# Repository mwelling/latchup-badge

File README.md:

# Fossi LATCH-UP Badge (Unofficial)

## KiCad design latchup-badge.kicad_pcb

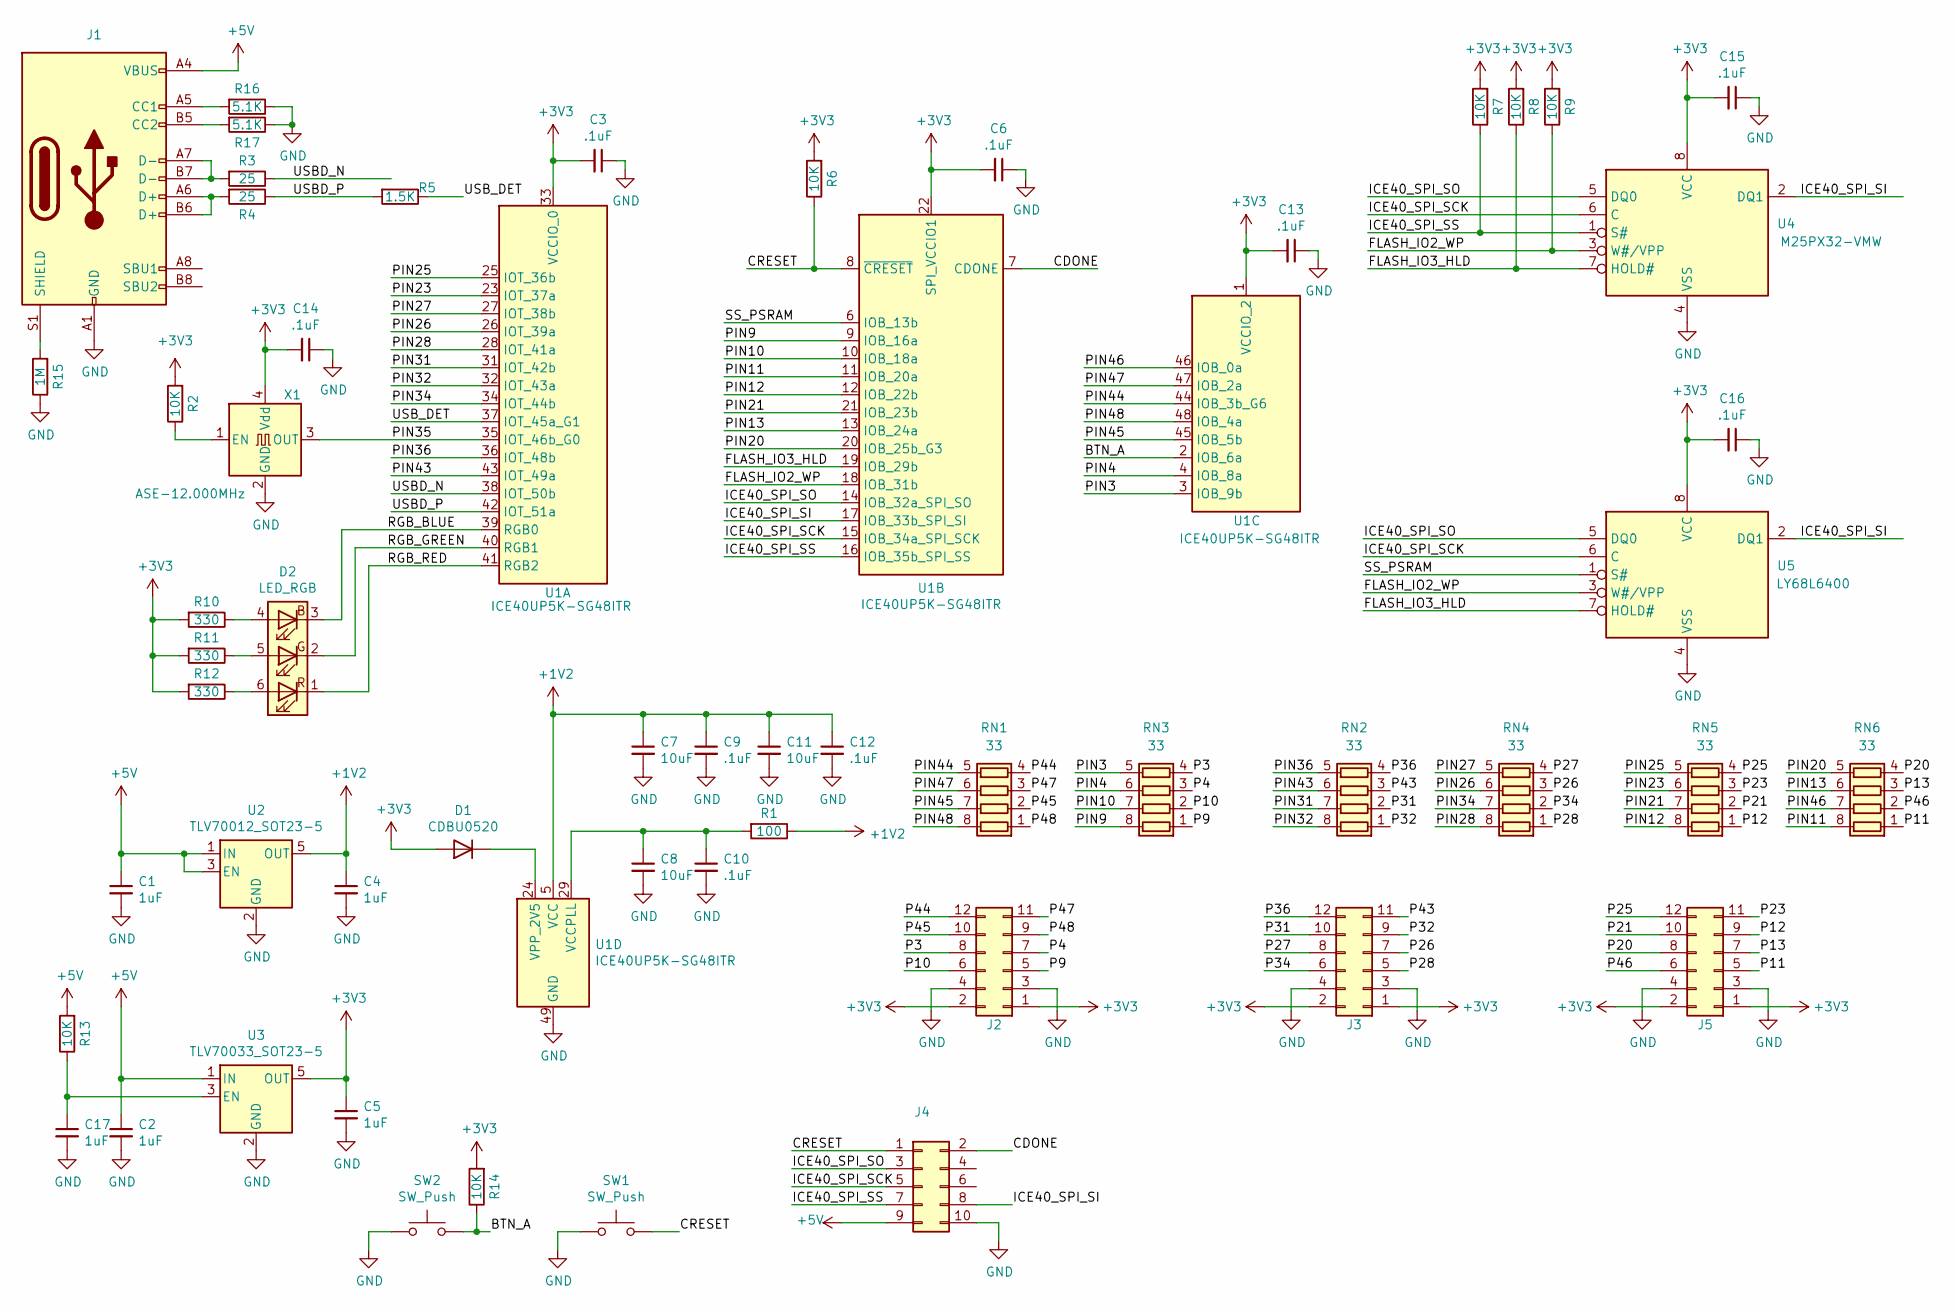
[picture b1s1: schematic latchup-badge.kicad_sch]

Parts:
C1, C2, C4, C5, C17: 1uF; C_0603_1608Metric
C3, C6, C9, C10, C12, C13, C14, C15, C16: .1uF; C_0402_1005Metric
C7, C8, C11: 10uF; C_0603_1608Metric
D1: CDBU0520; D_0603_1608Metric
D2: LED_RGB; LED_RGB_PLLC-6
J1: USB_C_Receptacle_USB2.0; USB_C_Receptacle_HRO_TYPE-C-31-M-12
J2, J3, J5: Connector_Generic:Conn_02x06_Odd_Even; PinSocket_2x06_P2.54mm_Horizontal
J4: Connector_Generic:Conn_02x05_Odd_Even; PinSocket_2x05_P2.54mm_Vertical
R1: 100; R_0402_1005Metric
R2, R6, R7, R8, R9, R13, R14: 10K; R_0402_1005Metric
R3, R4: 25; R_0402_1005Metric
R5: 1.5K; R_0402_1005Metric
R10, R11, R12: 330; R_0402_1005Metric
R15: 1M; R_0402_1005Metric
R16, R17: 5.1K; R_0402_1005Metric
RN1, RN2, RN3, RN4, RN5, RN6: 33; R_Array_Concave_4x0402
SW1, SW2: SW_Push; SW_SPST_EVQQ2
U1: ICE40UP5K-SG48ITR; QFN-48-1EP_7x7mm_P0.5mm_EP5.6x5.6mm
U2: TLV70012_SOT23-5; SOT-23-5
U3: TLV70033_SOT23-5; SOT-23-5
U4: M25PX32-VMW; SOIC-8W_5.3x5.3mm_P1.27mm
U5: LY68L6400; SOIC-8_3.9x4.9mm_P1.27mm
X1: ASE-12.000MHz; Oscillator_SMD_Abracon_ASE-4Pin_3.2x2.5mm

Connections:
+1V2: C4.1, C7.1, C9.1, C11.1, C12.1, R1.1, U1.5 (VCC), U1.30 (VCC), U2.5 (OUT)
+3V3: C3.2, C5.1, C6.2, C13.2, C14.2, C15.2, C16.2, D1.2 (A), J2.1, J2.2, J3.1, J3.2, J5.1, J5.2, R2.2, R6.2, R7.2, R8.2, R9.2, R10.2, R11.2, R12.2, R14.2, U1.1 (VCCIO_2), U1.22 (SPI_VCCIO1), U1.33 (VCCIO_0), U3.5 (OUT), U4.8 (VCC), U5.8 (VCC), X1.4 (Vdd)
+5V: C1.1, C2.1, J1.A4 (VBUS), J1.A9 (VBUS), J1.B4 (VBUS), J1.B9 (VBUS), J4.9, R13.2, U2.1 (IN), U2.3 (EN), U3.1 (IN)
/BTN_A: R14.1, SW2.2, U1.2 (IOB_6a)
/CDONE: J4.2, U1.7 (CDONE)
/CRESET: J4.1, R6.1, SW1.2, U1.8 (~CRESET)
/FLASH_IO2_WP: R9.1, U1.18 (IOB_31b), U4.3 (W#/VPP), U5.3 (W#/VPP)
/FLASH_IO3_HLD: R8.1, U1.19 (IOB_29b), U4.7 (HOLD#), U5.7 (HOLD#)
/ICE40_SPI_SCK: J4.5, U1.15 (IOB_34a_SPI_SCK), U4.6 (C), U5.6 (C)
/ICE40_SPI_SI: J4.8, U1.17 (IOB_33b_SPI_SI), U4.2 (DQ1), U5.2 (DQ1)
/ICE40_SPI_SO: J4.3, U1.14 (IOB_32a_SPI_SO), U4.5 (DQ0), U5.5 (DQ0)
/ICE40_SPI_SS: J4.7, R7.1, U1.16 (IOB_35b_SPI_SS), U4.1 (S#)
/P3: J2.8, RN3.4 (R4.1)
/P4: J2.7, RN3.3 (R3.1)
/P9: J2.5, RN3.1 (R1.1)
/P10: J2.6, RN3.2 (R2.1)
/P11: J5.5, RN6.1 (R1.1)
/P12: J5.9, RN5.1 (R1.1)
/P13: J5.7, RN6.3 (R3.1)
/P20: J5.8, RN6.4 (R4.1)
/P21: J5.10, RN5.2 (R2.1)
/P23: J5.11, RN5.3 (R3.1)
/P25: J5.12, RN5.4 (R4.1)
/P26: J3.7, RN4.3 (R3.1)
/P27: J3.8, RN4.4 (R4.1)
/P28: J3.5, RN4.1 (R1.1)
/P31: J3.10, RN2.2 (R2.1)
/P32: J3.9, RN2.1 (R1.1)
/P34: J3.6, RN4.2 (R2.1)
/P36: J3.12, RN2.4 (R4.1)
/P43: J3.11, RN2.3 (R3.1)
/P44: J2.12, RN1.4 (R4.1)
/P45: J2.10, RN1.2 (R2.1)
/P46: J5.6, RN6.2 (R2.1)
/P47: J2.11, RN1.3 (R3.1)
/P48: J2.9, RN1.1 (R1.1)
/PIN3: RN3.5 (R4.2), U1.3 (IOB_9b)
/PIN4: RN3.6 (R3.2), U1.4 (IOB_8a)
/PIN9: RN3.8 (R1.2), U1.9 (IOB_16a)
/PIN10: RN3.7 (R2.2), U1.10 (IOB_18a)
/PIN11: RN6.8 (R1.2), U1.11 (IOB_20a)
/PIN12: RN5.8 (R1.2), U1.12 (IOB_22b)
/PIN13: RN6.6 (R3.2), U1.13 (IOB_24a)
/PIN20: RN6.5 (R4.2), U1.20 (IOB_25b_G3)
/PIN21: RN5.7 (R2.2), U1.21 (IOB_23b)
/PIN23: RN5.6 (R3.2), U1.23 (IOT_37a)
/PIN25: RN5.5 (R4.2), U1.25 (IOT_36b)
/PIN26: RN4.6 (R3.2), U1.26 (IOT_39a)
/PIN27: RN4.5 (R4.2), U1.27 (IOT_38b)
/PIN28: RN4.8 (R1.2), U1.28 (IOT_41a)
/PIN31: RN2.7 (R2.2), U1.31 (IOT_42b)
/PIN32: RN2.8 (R1.2), U1.32 (IOT_43a)
/PIN34: RN4.7 (R2.2), U1.34 (IOT_44b)
/PIN35: U1.35 (IOT_46b_G0), X1.3 (OUT)
/PIN36: RN2.5 (R4.2), U1.36 (IOT_48b)
/PIN43: RN2.6 (R3.2), U1.43 (IOT_49a)
/PIN44: RN1.5 (R4.2), U1.44 (IOB_3b_G6)
/PIN45: RN1.7 (R2.2), U1.45 (IOB_5b)
/PIN46: RN6.7 (R2.2), U1.46 (IOB_0a)
/PIN47: RN1.6 (R3.2), U1.47 (IOB_2a)
/PIN48: RN1.8 (R1.2), U1.48 (IOB_4a)
/RGB_BLUE: D2.3 (BK), U1.39 (RGB0)
/RGB_GREEN: D2.2 (GK), U1.40 (RGB1)
/RGB_RED: D2.1 (RK), U1.41 (RGB2)
/SS_PSRAM: U1.6 (IOB_13b), U5.1 (S#)
/USBD_N: R3.1, U1.38 (IOT_50b)
/USBD_P: R4.1, R5.2, U1.42 (IOT_51a)
/USB_DET: R5.1, U1.37 (IOT_45a_G1)
GND: C1.2, C2.2, C3.1, C4.2, C5.2, C6.1, C7.2, C8.2, C9.2, C10.2, C11.2, C12.2, C13.1, C14.1, C15.1, C16.1, C17.2, J1.A1 (GND), J1.A12 (GND), J1.B1 (GND), J1.B12 (GND), J2.3, J2.4, J3.3, J3.4, J4.10, J5.3, J5.4, R15.1, R16.1, R17.1, SW1.1, SW2.1, U1.49 (GND), U2.2 (GND), U3.2 (GND), U4.4 (VSS), U5.4 (VSS), X1.2 (GND)
unnamed: C8.1, C10.1, R1.2, U1.29 (VCCPLL)
unnamed: C17.1, R13.1, U3.3 (EN)
unnamed: D1.1 (K), U1.24 (VPP_2V5)
unnamed: D2.4 (BA), R10.1
unnamed: D2.5 (GA), R11.1
unnamed: D2.6 (RA), R12.1
unnamed: J1.A5 (CC1), R16.2
unnamed: J1.A6 (D+), J1.B6 (D+), R4.2
unnamed: J1.A7 (D-), J1.B7 (D-), R3.2
unnamed: J1.B5 (CC2), R17.2
unnamed: J1.S1 (SHIELD), R15.2
unnamed: R2.1, X1.1 (EN)

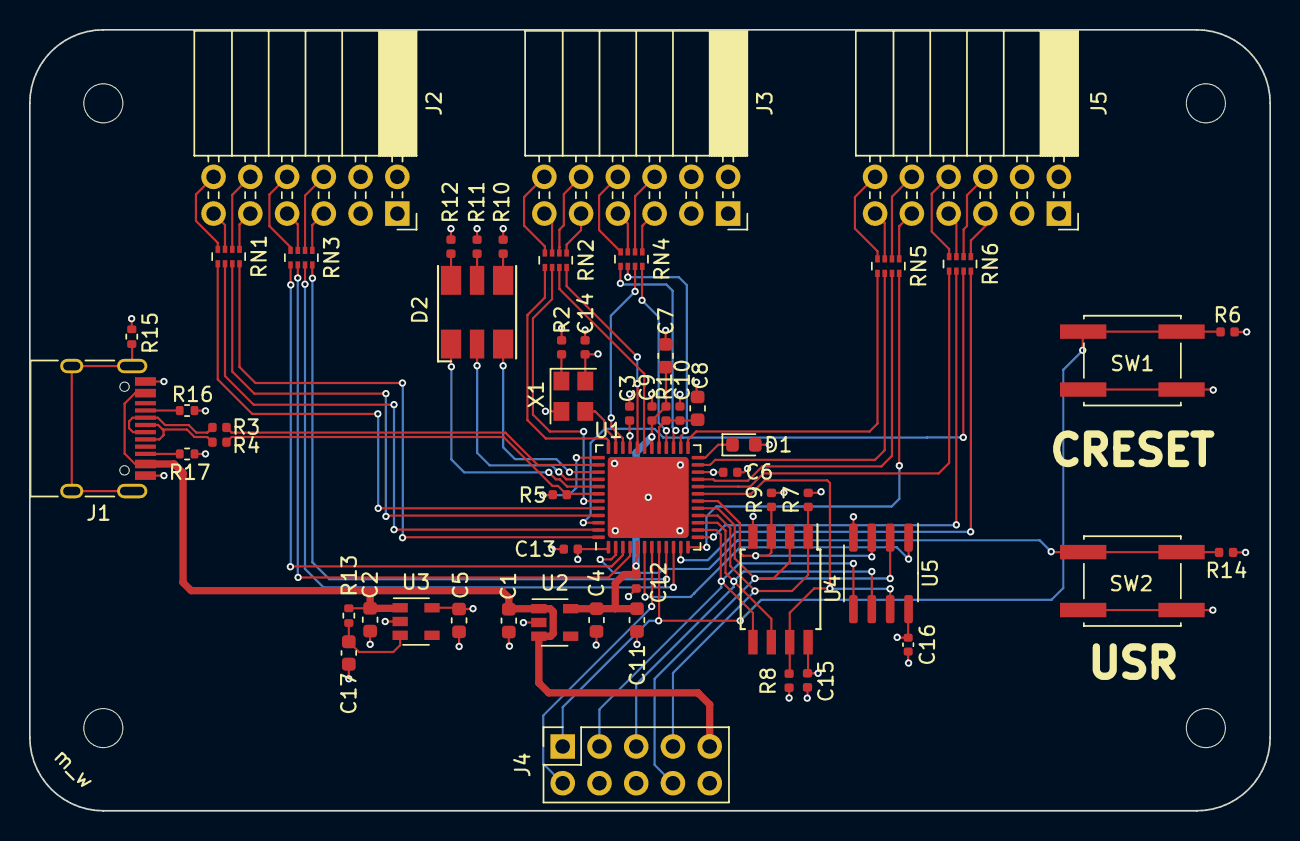
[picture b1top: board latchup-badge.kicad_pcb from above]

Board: 4 copper layers, 85.7 x 54.0 mm, 55 parts (0 on the bottom side), 81 nets.

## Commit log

2019-03-28 Add some initial circuitry
    Adds ICE40, regulators, SPI flash.
2019-04-11 Moar updates
2019-04-14 Add some artwork
2019-04-15 Add some headers and route
    Some small tweaks left but mostly done.
2019-04-16 OSHPark is sponsoring the PCBs!
2019-04-16 Tweak routing per review from tnt
    Gives the GND plane more room to breathe.
2019-04-16 Add RGB and a few buttons
    Ready final review.
2019-04-16 See everyone at Latchup!
    This is puppy is going to the fab.
2024-02-08 Update gitignore
2024-02-08 Update to Kicad 6
2024-02-12 Switch to USB-C connector and shrink board
2024-03-02 Add PSRAM
2024-03-04 Update PSRAM footprint
2024-03-04 Use the PMOD pinout from icebreaker bitsy breakout
2024-03-04 Add delay to 3.3V enable
    The 1.2V rail should be up before 3.3V.
2024-03-04 Add series damping resistors on PMODs
2024-04-14 Routed board
    Switched to 4 layer design and routed it.
